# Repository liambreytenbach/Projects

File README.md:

## Project Portfolio - Liam Breytenbach
**Last Updated:** 27 August 2025  

## Overview
This repository contains 10 projects I have completed. Each project explores different areas of engineering and programming, ranging from embedded systems to game development. I have also included projects that highlight my mechanical and electrical engineering skills.

## Requirements
To view or run the projects, you may need the following software:
- MATLAB
- Jupyter Notebook
- STM32CubeMX
- GameMaker
- Unity
- KiCad
- PrusaSlicer

## Project Structure
Each project folder includes:
- Project Description
- Report (written explanations)
- Summary (where necessary) highlighting the main accomplishments or practical uses
- Source code and/or models  

## Usage
For each project, open its folder and review the project description and summary/report to better understand the objectives and outcomes.

## Contact
If you have any questions or would like more information:  
Email: liam.breytenbach@email.com

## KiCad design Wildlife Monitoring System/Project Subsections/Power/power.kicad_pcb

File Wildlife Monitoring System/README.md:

## Wildlife Monitoring System - Liam Breytenbach
**Last Updated:** 28 August 2025  

## Project Description
This project involved designing and building a camera system, encased in a custom housing, to monitor Fork-tailed Drongos during twilight feeding. The system enabled remote observation of bird behavior and predation activity, providing an elegant solution for collecting ecological data in hard-to-access locations. My assigned role focused on the design and development of the housing submodule.

## Requirements
To run or view the Housing Submodule, you may need the following software/applications:
- SolidWorks
- PrusaSlicer

## Project Contents
This folder includes:
- Project Description
- Report
- Summary
- Source Code and Models

## Usage
Open this folder and review the project description, report, and summary. Each subsection has been placed in a separate folder: Came, GUI,  Power and Housing Subsection.

## Contact
If you have any questions or would like more information:  
Email: liam.breytenbach@email.com

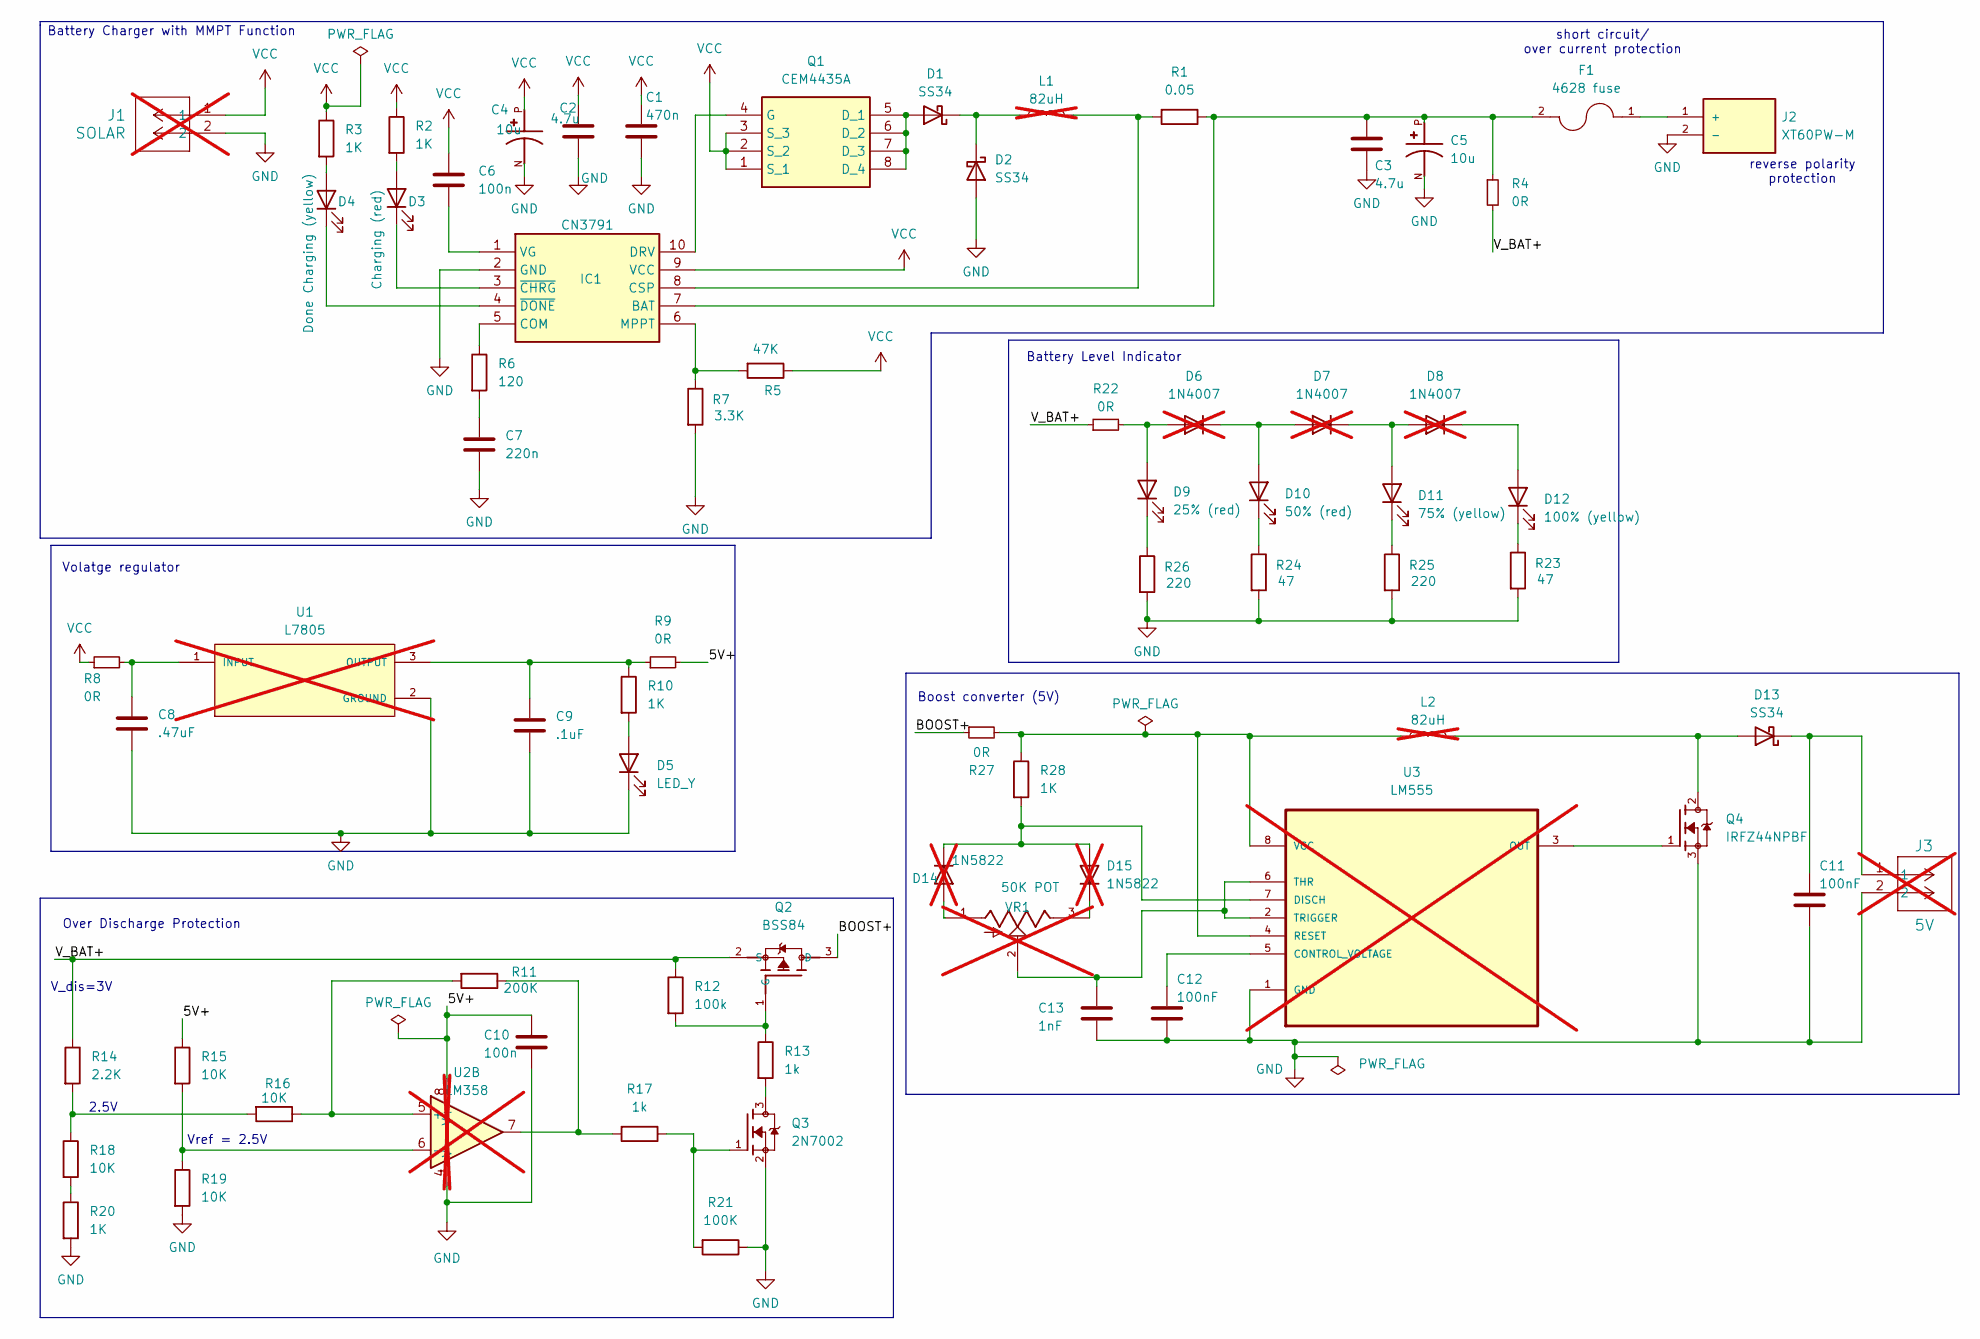
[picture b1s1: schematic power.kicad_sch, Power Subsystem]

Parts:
C1: 470n; C_0805_2012Metric
C2, C3: 4.7u; C_0805_2012Metric
C4, C5: 10u; CAPAE660X610N; PARTREV CAT.8100K
C6, C10: 100n; C_0805_2012Metric
C7: 220n; C_0805_2012Metric
C8: .47uF; C_0805_2012Metric
C9: .1uF; C_0805_2012Metric
C11, C12: 100nF; C_0805_2012Metric
C13: 1nF; C_0805_2012Metric
D1, D2, D13: SS34; D_SMA
D3: Charging (red); LED_0603_1608Metric
D4: Done Charging (yellow); LED_0603_1608Metric
D5: LED_Y; LED_0603_1608Metric
D6, D7, D8: 1N4007; D_DO-41_SOD81_P10.16mm_Horizontal; not fitted
D9: 25% (red); LED_0603_1608Metric
D10: 50% (red); LED_0603_1608Metric
D11: 75% (yellow); LED_0603_1608Metric
D12: 100% (yellow); LED_0603_1608Metric
D14, D15: 1N5822; D_DO-41_SOD81_P10.16mm_Horizontal; not fitted
F1: 4628 fuse; FUSE_4628
IC1: CN3791; SOP100P600X175-10N; Manufacturer_Part_Number CN3791
J1: SOLAR; CONN_DG128_DEG; not fitted
J2: XT60PW-M; AMASS_XT60PW-M; PARTREV V1.2
J3: 5V; CONN_DG128_DEG; not fitted
L1, L2: 82uH; R_Axial_Power_L20.0mm_W6.4mm_P5.08mm_Vertical; not fitted
Q1: CEM4435A; SOIC127P600X175-8N; Manufacturer_Part_Number CEM4435A
Q2: BSS84; SOT95P240X120-3N
Q3: 2N7002; SOT95P240X111-3N; PARTREV 4
Q4: IRFZ44NPBF; TO254P1016X419X2286-3; PARTREV 09/21/10
R1: 0.05; R_1210_3225Metric
R2, R3, R10, R20, R28: 1K; R_0805_2012Metric
R4, R8, R9, R22, R27: 0R; R_0805_2012Metric
R5: 47K; R_0805_2012Metric
R6: 120; R_0805_2012Metric
R7: 3.3K; R_0805_2012Metric
R11: 200K; R_0805_2012Metric
R12: 100k; R_0805_2012Metric
R13, R17: 1k; R_0805_2012Metric
R14: 2.2K; R_0805_2012Metric
R15, R16, R18, R19: 10K; R_0805_2012Metric
R21: 100K; R_0805_2012Metric
R23, R24: 47; R_0805_2012Metric
R25, R26: 220; R_0805_2012Metric
U1: L7805; TO255P1040X460X1968-3; PARTREV 36; not fitted
U2: LM358; DIP794W45P254L1016H508Q8; not fitted
U3: LM555; DIP254P762X533-8; MPN LM555CN; not fitted
VR1: 50K POT; TRIM_3362P-1-503LF; PARTREV 08/26/10; not fitted

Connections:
/5V+: C10.1, R9.2, R15.1, U2.8 (V+)
/BOOST+: Q2.3 (D), R27.1
/V_BAT+: Q2.2 (S), R4.2, R12.1, R14.1, R22.1
GND: C1.2, C2.2, C3.2, C4.N, C5.N, C7.2, C8.2, C9.2, C10.2, C11.2, C12.2, C13.2, D2.2 (A), D5.1 (K), IC1.2 (GND), J1.2, J2.2 (-), J3.2, Q3.2, Q4.3, R7.2, R19.2, R20.2, R21.1, R23.2, R24.2, R25.2, R26.2, U1.2 (GROUND), U2.4 (V-), U3.1 (GND)
unnamed: C7.1, R6.2
unnamed: D1.2 (A), Q1.5 (D_1), Q1.6 (D_2), Q1.7 (D_3), Q1.8 (D_4)
unnamed: D1.1 (K), D2.1 (K), L1.1
unnamed: D3.2 (A), R2.2
unnamed: D3.1 (K), IC1.3 (~CHRG)
unnamed: D4.2 (A), R3.2
unnamed: D4.1 (K), IC1.4 (~DONE)
unnamed: D5.2 (A), R10.2
unnamed: D6.2 (A), D9.2 (A), R22.2
unnamed: D9.1 (K), R26.1
unnamed: D6.1 (K), D7.2 (A), D10.2 (A)
unnamed: D10.1 (K), R24.1
unnamed: D7.1 (K), D8.2 (A), D11.2 (A)
unnamed: D11.1 (K), R25.1
unnamed: D8.1 (K), D12.2 (A)
unnamed: D12.1 (K), R23.1
unnamed: D13.2 (A), L2.2, Q4.2
unnamed: C11.1, D13.1 (K), J3.1
unnamed: D14.2 (A), VR1.1
unnamed: D14.1 (K), D15.2 (A), R28.2, U3.7 (DISCH)
unnamed: D15.1 (K), VR1.3
unnamed: C3.1, C5.P, F1.2, IC1.7 (BAT), R1.1, R4.1
unnamed: IC1.5 (COM), R6.1
unnamed: IC1.8 (CSP), L1.2, R1.2
unnamed: IC1.10 (DRV), Q1.4 (G)
unnamed: IC1.6 (MPPT), R5.2, R7.1
unnamed: C6.2, IC1.1 (VG)
unnamed: F1.1, J2.1 (+)
unnamed: Q2.1 (G), R12.2, R13.1
unnamed: Q3.1, R17.1, R21.2
unnamed: Q3.3, R13.2
unnamed: R11.1, R17.2, U2.7
unnamed: R14.2, R16.2, R18.1
unnamed: R18.2, R20.1
unnamed: C8.1, R8.2, U1.1 (INPUT)
unnamed: C9.1, R9.1, R10.1, U1.3 (OUTPUT)
unnamed: R11.2, R16.1, U2.5 (+)
unnamed: R15.2, R19.1, U2.6 (-)
unnamed: C12.1, U3.5 (CONTROL_VOLTAGE)
unnamed: Q4.1, U3.3 (OUT)
unnamed: L2.1, R27.2, R28.1, U3.4 (RESET), U3.8 (VCC)
unnamed: C13.1, U3.2 (TRIGGER), U3.6 (THR), VR1.2
VCC: C1.1, C2.1, C4.P, C6.1, IC1.9 (VCC), J1.1, Q1.1 (S_1), Q1.2 (S_2), Q1.3 (S_3), R2.1, R3.1, R5.1, R8.1

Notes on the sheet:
Over Discharge Protection
Vref = 2.5V
short circuit/ over current protection
Boost converter (5V)
V_dis=3V
reverse polarity protection
Battery Level Indicator
Volatge regulator
2.5V
Battery Charger with MMPT Function

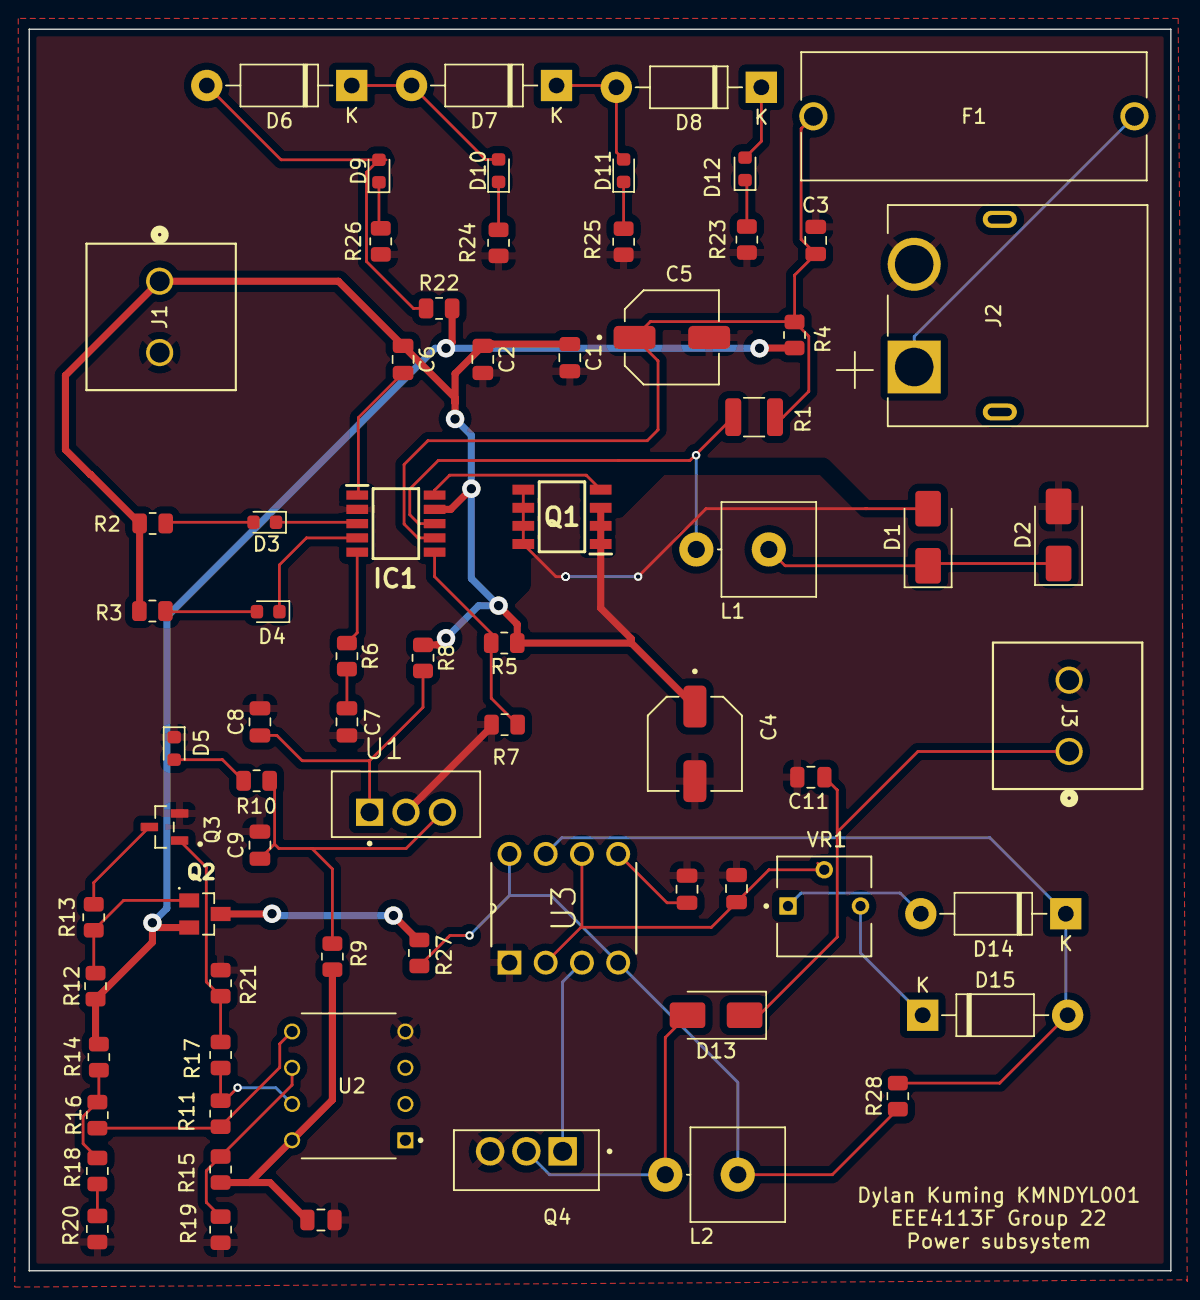
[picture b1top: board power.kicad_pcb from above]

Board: 2 copper layers, 80.0 x 87.0 mm, 71 parts (0 on the bottom side), 47 nets.

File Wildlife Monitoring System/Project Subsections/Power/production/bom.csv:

Designator,Footprint,Quantity,Value,LCSC Part #
C1,0805,1,470n,
"C10, C6",0805,2,100n,
"C11, C12",0805,2,100nF,
C13,0805,1,1nF,
"C2, C3",0805,2,4.7u,
"C4, C5",CAPAE660X610N,2,10u,
C7,0805,1,220n,
C8,0805,1,.47uF,
C9,0805,1,.1uF,
"D1, D13, D2",D_SMA,3,SS34,
D10,0603,1,50% (red),
D11,0603,1,75% (yellow),
D12,0603,1,100% (yellow),
D3,0603,1,Charging (red),
D4,0603,1,Done Charging (yellow),
D5,0603,1,LED_Y,
D9,0603,1,25% (red),
F1,FUSE_4628,1,4628 fuse,
IC1,SOP100P600X175-10N,1,CN3791,
J2,AMASS_XT60PW-M,1,XT60PW-M,
Q1,SOIC127P600X175-8N,1,CEM4435A,
Q2,SOT95P240X120-3N,1,BSS84,
Q3,SOT95P240X111-3N,1,2N7002,
Q4,TO254P1016X419X2286-3,1,IRFZ44NPBF,
R1,1210,1,0.05,
"R10, R13, R17, R2, R20, R28, R3",0805,7,1K,
R11,0805,1,200K,
"R12, R21",0805,2,100k,
R14,0805,1,2.2K,
"R15, R16, R18, R19",0805,4,10K,
"R22, R27, R4, R8, R9",0805,5,0R,
"R23, R24",0805,2,47,
"R25, R26",0805,2,220,
R5,0805,1,47K,
R6,0805,1,120,
R7,0805,1,3.3K,

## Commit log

2025-08-28 Add Basic Fiber-Optics Project folder
2025-08-28 Add Engineering Thesis folder
2025-08-28 README.md
2025-08-28 Add Escape Room Puzzle folder
2025-08-28 Add FOC algorithm for a surface PM motor folder
2025-08-28 Rename READ ME.md to README.md
2025-08-28 Rename READ ME.txt to README.md
2025-08-28 Add Medical Imaging and Image Processing folder
2025-08-28 Add Modulation & Demodulation folder
2025-08-28 Add Self Driving Robotic Car folder
2025-08-28 Track large files with Git LFS
2025-08-28 Add Summary.mp4 via Git LFS
2025-08-28 Add Summary.mp4 to Self Driving Robotic Car folder
2025-08-28 Add Weather Station folder
2025-08-28 Add Wildlife Monitoring System folder
2025-08-28 Add Summary.pdf to IOS Game folder
